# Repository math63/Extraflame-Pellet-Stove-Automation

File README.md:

# Extraflame-Pellet-Stove-Automation

https://pcbs.io/share/42JMy

https://www.sculpteo.com/fr/print_old/boite_v2-10/cqvDiYiF?basket=1&noclickredirect=1&uuid=6ML2Aqv1MtEUXSKbfupsUg

https://circuits.io/circuits/5604341-arduinorfm95-v6

Comments :
In mysensors plugin for jeedom, change baudrate from 115200 to 38400 :
Mysensors/Node/mysensors.js

```
var SerialPort = require('serialport');
	gw = new SerialPort(gwAddress);
        //compatibilité avec la nouvelle verion de serialport
        if ( gw.settings.baudRate ){
                gw.settings.baudRate=38400;
        }else{
                gw.settings.baudrate=38400;
        }
```

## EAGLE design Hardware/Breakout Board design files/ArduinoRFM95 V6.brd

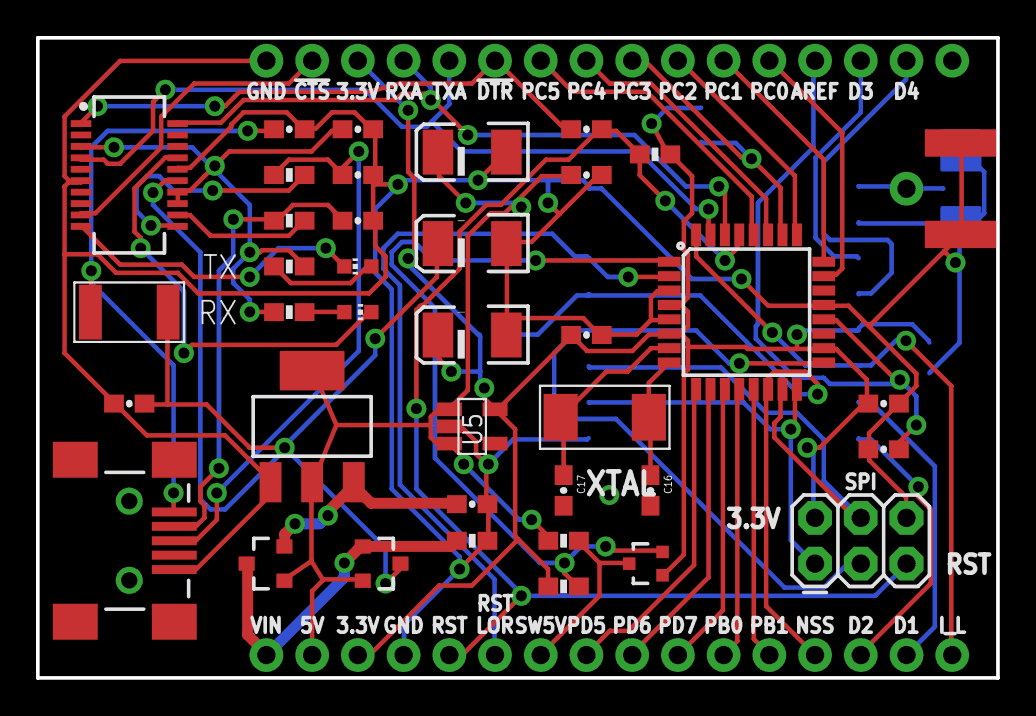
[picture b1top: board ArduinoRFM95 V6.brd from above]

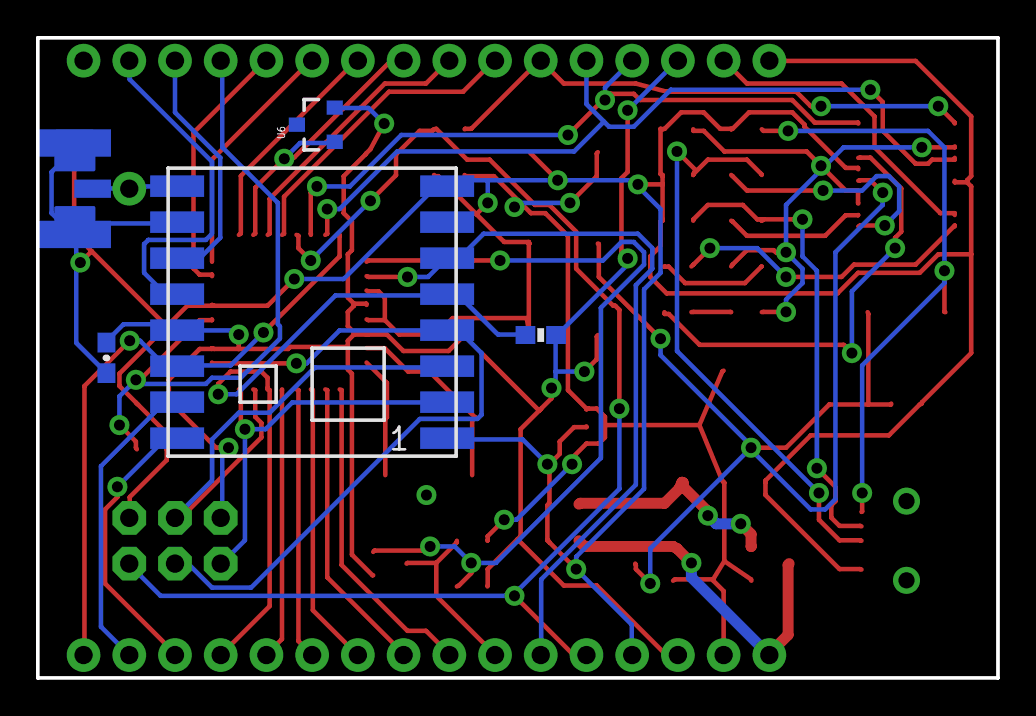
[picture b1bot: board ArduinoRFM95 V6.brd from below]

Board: 2 copper layers, 53.3 x 35.6 mm, 46 parts (5 on the bottom side), 48 nets.

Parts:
C1, C2, C3, C5, C6, C9, C10, C11, C15: 0.1uF; 0603-CAP
C4, C12, C14: 10uF; EIA3528-KIT
C7, C8: 47pF; 0603-CAP
C13: 1uF; 0603-CAP
C16, C17: 18pF; 0603-CAP
D1: YELLOW; CHIP-LED0603
D2: RED; CHIP-LED0603
F1: MF-MSMF050-2; F1812
FRAME1: FRAME-LETTER; CREATIVE_COMMONS
J2: AVR_SPI_PRG_6PTH; 2X3
J3: USB-SMD-NS; USB-MINIB-NOSTOP
J4, J5: 1X16_NO_SILK
JP3: 1X01NS-KIT
Q1: FDN360P; SOT23-3
Q2: MOSFET-NCHANNEL2N7002PW; SOT323
Q3: PMV48XP; SOT23-3
R1, R4, R5, R8: 10K; 0603-RES
R2, R3: 27R; 0603-RES
R6, R7: 470R; 0603-RES
R9: 100K; 0603-RES
U1: ATMEGA328P_TQFP; TQFP32-08
U2: RFM69HCW; RFM69HCW-XXXS2
U3: FT231XS; SSOP20_L
U4: NCP1117ST50T3G; SOT223
U5: LP2992-33; SOT-23-5
U6: ATSHA204-TSU; SOT23-3
X1: SMA_EDGELAUNCH_UFL
XTAL: AMB7; 2-SMD_ABM7

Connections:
3.3V: C1.2, C13.2, C14.A, C15.2, J2.2, J4.3, J5.3, Q2.1, R1.2, R5.1, R9.2, U1.4, U1.6, U1.18, U2.13, U5.5, U6.2
3.3V_FTDI: C9.2, R6.1, R7.1, U3.3, U3.13, U3.14
5V: C4.A, C5.2, J5.2, Q1.2, Q3.1, R4.1, U4.2, U4.4, U5.1, U5.3
!CTS: J4.2, U3.9
!DTR: C3.2, J4.6, U3.1
ANT: JP3.1, U2.9, X1.P
AREF: C6.2, J4.13, U1.20
DIO1_LORA: J5.15, U2.15
DIO2_LORA: J5.14, U2.16
DIO3_LORA: J4.14, U2.11
DIO4_LORA: J4.15, U2.12
GND: C1.1, C2.1, C4.C, C5.1, C6.1, C7.1, C8.1, C9.1, C10.1, C11.1, C12.C, C13.1, C14.C, C15.1, C16.2, C17.2, J2.6, J3.GND, J4.1, J5.4, R8.1, U1.3, U1.5, U1.21, U2.1, U2.8, U2.10, U3.6, U3.16, U4.1, U5.2, U6.3, X1.GND@1, X1.GND@2, X1.GND@3, X1.GND@4
INT_LORA: J5.16, U1.32, U2.14
MISO: J2.1, U1.16, U2.2
MOSI: J2.4, U1.15, U2.3
unnamed: R3.1, U3.11
unnamed: C7.2, J3.D-, R2.2
unnamed: C2.2, Q3.2, U4.3
unnamed: R2.1, U3.12
unnamed: C10.2, F1.1, J3.VBUS
unnamed: C17.1, U1.7, XTAL.P$2
unnamed: D2.C, U3.10
unnamed: C16.1, U1.8, XTAL.P$1
unnamed: C8.2, J3.D+, R3.2
unnamed: D1.C, U3.17
PB0: J5.11, U1.12
PB1: J5.12, U1.13
PC0: J4.12, U1.23
PC1: J4.11, U1.24
PC2: J4.10, U1.25
PC3: J4.9, U1.26, U6.1
PC4: J4.8, U1.27
PC5: J4.7, U1.28
PD5: J5.8, U1.9
PD6: J5.9, U1.10
PD7: J5.10, U1.11
RESET: C3.1, J2.5, J5.5, R1.1, U1.29
RST_LORA: J5.6, U1.2, U2.6
RX_AT: J4.4, U1.30, U3.20
RX_LED: D1.A, R6.2
SCK: J2.3, U1.17, U2.4
SS: J5.13, R9.1, U1.14, U2.5
SW_3.3V: Q2.2, R5.2, U1.1
SW_5V: J5.7, Q2.3, R4.2
TX_AT: J4.5, U1.31, U3.4
TX_LED: D2.A, R7.2
VIN: J5.1, Q1.1, Q3.3, R8.2
VUSB: C11.2, C12.A, F1.2, Q1.3, U3.15

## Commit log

2017-10-16 Create test
2017-10-22 add lib
2017-11-01 add pdf
2017-11-01 svg + build links
2017-11-02 circuits.io link added
2017-11-19 ino files
    add mysensors files
2017-11-19 add comment
2021-11-21 V2.2 files

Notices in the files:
parts and their libraries:
SparkFun-Capacitors: Licensing: Creative Commons ShareAlike 4.0 International - https://creativecommons.org/licenses/by-sa/4.0
SparkFun-Retired: Released under the Creative Commons Attribution Share-Alike 3.0 License
SparkFun-Retired: https://creativecommons.org/licenses/by-sa/3.0
